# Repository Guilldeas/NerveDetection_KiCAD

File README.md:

### Content

This repo stores KiCAD files for the development of a low noise preamplifier employing the gradiometer technique. Some symbols where custom made for the schematic and were provided on the Samac_Sys folder. User must add this folder to the KiCAD library path list to correctly visualize the schematics.

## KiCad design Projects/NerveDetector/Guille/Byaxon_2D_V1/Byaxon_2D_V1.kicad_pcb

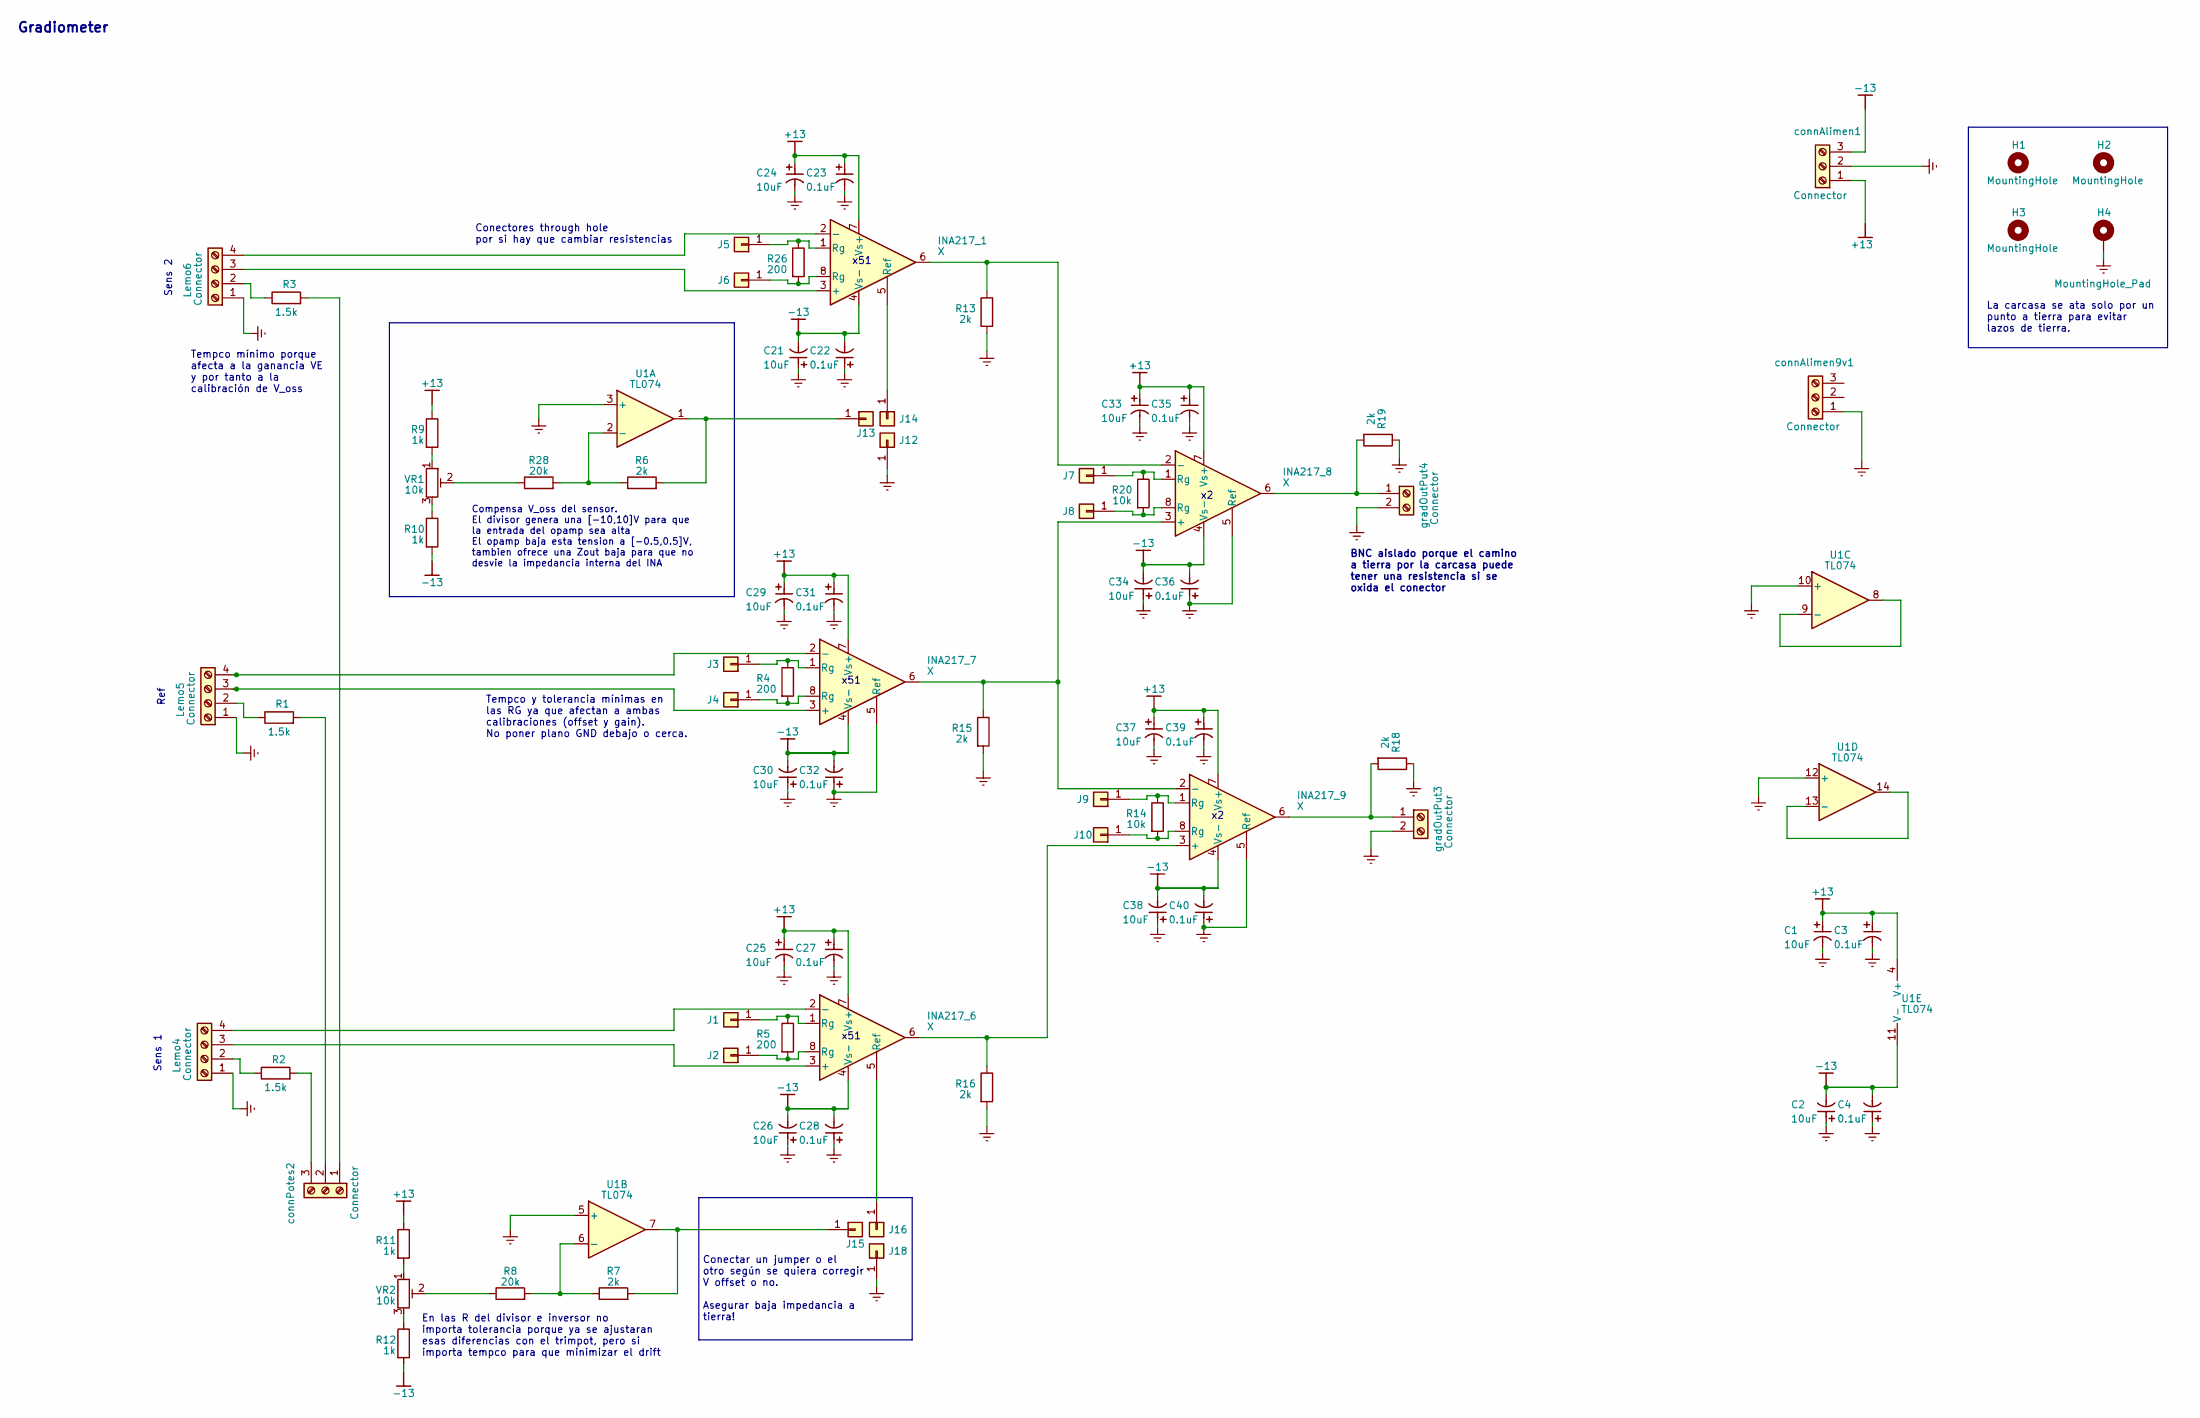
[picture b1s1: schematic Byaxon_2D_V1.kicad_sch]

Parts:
C1, C2, C21, C24, C25, C26, C29, C30, C33, C34, C37, C38: 10uF; CP_EIA-7132-20_AVX-U_Pad2.72x3.50mm_HandSolder
C3, C4, C22, C23, C27, C28, C31, C32, C35, C36, C39, C40: 0.1uF; CP_EIA-3216-10_Kemet-I_Pad1.58x1.35mm_HandSolder
H1, H2, H3: MountingHole; MountingHole_3.2mm_M3
H4: MountingHole_Pad; MountingHole_3.2mm_M3_DIN965_Pad
INA217_1, INA217_7, INA217_8, INA217_9: X; DIP-8_W7.62mm_Acid_Etch_Limitations
INA217_6: X; DIP-8_W7.62mm
J1, J2, J3, J4, J5, J6, J7, J8, J9, J10, J12, J13, J14, J15, J16, J18: Pin_D0.7mm_L6.5mm_W1.8mm_FlatFork
Lemo4, Lemo5, Lemo6: Connector; TerminalBlock_Phoenix_MPT-0,5-4-2.54_1x04_P2.54mm_Horizontal
R1, R2, R3: 1.5k; ERJ1T__2512_; Mouser Part Number 667-ERJ-1TNF1501U
R4, R5, R26: 200; RESC3016X65N; Mouser Part Number 708-RNCF1206TKY200R
R6, R7: 2k; R_0402_1005Metric_Pad0.72x0.64mm_HandSolder_Acid_Etch_Limit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; Mouser Part Number 667-ERA-2ARC202X
R8, R28: 20k; R_0402_1005Metric_Pad0.72x0.64mm_HandSolder_Acid_Etch_Limit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
R9, R10, R11, R12: 1k; RESC1608X60N; Mouser Part Number 754-RR0816P-102D
R13, R15, R16, R18, R19: 2k; RESC1005X40N_Acid_Etch_Limitations; Mouser Part Number 660-RK73H1ETTP2001F
R14, R20: 10k; RESC3016X65N; Mouser Part Number 708-RNCF1206TKY200R
U1: TL074; DIP794W53P254L1930H508Q14N_Acid_Etch_Limitations; Manufacturer_Part_Number TL074CN
VR1, VR2: 10k; 3362P_1_Acid_Etch_Limitations; Mouser Part Number 652-3362P-1-103LF
connAlimen1, connAlimen9v1: Connector; TerminalBlock_Phoenix_MPT-0,5-3-2.54_1x03_P2.54mm_Horizonta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
connPotes2: Connector; TerminalBlock_Phoenix_MPT-0,5-3-2.54_1x03_P2.54mm_Horizonta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
gradOutPut3, gradOutPut4: Connector; TerminalBlock_Phoenix_MPT-0,5-2-2.54_1x02_P2.54mm_Horizonta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

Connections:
+13: C1.2, C3.2, C23.2, C24.2, C25.2, C27.2, C29.2, C31.2, C33.2, C35.2, C37.2, C39.2, INA217_1.7 (Vs+), INA217_6.7 (Vs+), INA217_7.7 (Vs+), INA217_8.7 (Vs+), INA217_9.7 (Vs+), R9.1, R11.1, U1.4 (V+), connAlimen1.1
-13: C2.1, C4.1, C21.1, C22.1, C26.1, C28.1, C30.1, C32.1, C34.1, C36.1, C38.1, C40.1, INA217_1.4 (Vs-), INA217_6.4 (Vs-), INA217_7.4 (Vs-), INA217_8.4 (Vs-), INA217_9.4 (Vs-), R10.2, R12.2, U1.11 (V-), connAlimen1.3
Earth: C1.1, C2.2, C3.1, C4.2, C21.2, C22.2, C23.1, C24.1, C25.1, C26.2, C27.1, C28.2, C29.1, C30.2, C31.1, C32.2, C33.1, C34.2, C35.1, C36.2, C37.1, C38.2, C39.1, C40.2, H4.1, INA217_7.5 (Ref), INA217_8.5 (Ref), INA217_9.5 (Ref), J12.1, J18.1, Lemo4.1, Lemo5.1, Lemo6.1, R13.2, R15.2, R16.2, R18.1, R19.1, U1.3 (+), U1.5 (+), U1.10 (+), U1.12 (+), connAlimen1.2, connAlimen9v1.1, gradOutPut3.2, gradOutPut4.2
unnamed: INA217_1.3 (+), Lemo6.3
unnamed: INA217_1.2 (-), Lemo6.4
unnamed: INA217_1.5 (Ref), J14.1
unnamed: INA217_6.3 (+), Lemo4.3
unnamed: INA217_6.2 (-), Lemo4.4
unnamed: INA217_6.5 (Ref), J16.1
unnamed: INA217_7.3 (+), Lemo5.3
unnamed: INA217_7.2 (-), Lemo5.4
unnamed: INA217_7.6, INA217_8.3 (+), INA217_9.2 (-), R15.1
unnamed: INA217_1.6, INA217_8.2 (-), R13.1
unnamed: INA217_6.6, INA217_9.3 (+), R16.1
unnamed: INA217_6.1 (Rg), J1.1, R5.1
unnamed: INA217_6.8 (Rg), J2.1, R5.2
unnamed: INA217_7.1 (Rg), J3.1, R4.1
unnamed: INA217_7.8 (Rg), J4.1, R4.2
unnamed: INA217_1.1 (Rg), J5.1, R26.1
unnamed: INA217_1.8 (Rg), J6.1, R26.2
unnamed: INA217_8.1 (Rg), J7.1, R20.1
unnamed: INA217_8.8 (Rg), J8.1, R20.2
unnamed: INA217_9.1 (Rg), J9.1, R14.1
unnamed: INA217_9.8 (Rg), J10.1, R14.2
unnamed: J13.1, R6.2, U1.1
unnamed: J15.1, R7.2, U1.7
unnamed: Lemo4.2, R2.1
unnamed: Lemo5.2, R1.1
unnamed: Lemo6.2, R3.1
unnamed: R8.1, VR2.2
unnamed: R9.2, VR1.1
unnamed: R10.1, VR1.3
unnamed: R11.2, VR2.1
unnamed: R12.1, VR2.3
unnamed: R28.1, VR1.2
unnamed: R6.1, R28.2, U1.2 (-)
unnamed: R7.1, R8.2, U1.6 (-)
unnamed: U1.8, U1.9 (-)
unnamed: U1.13 (-), U1.14
unnamed: R3.2, connPotes2.1
unnamed: R1.2, connPotes2.2
unnamed: R2.2, connPotes2.3
unnamed: INA217_9.6, R18.2, gradOutPut3.1
unnamed: INA217_8.6, R19.2, gradOutPut4.1

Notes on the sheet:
Gradiometer
Conectar un jumper o el otro según se quiera corregir V offset o no. Asegurar baja impedancia a tierra!
Compensa V_oss del sensor. El divisor genera una [-10,10]V para que la entrada del opamp sea alta El opamp baja esta tension a [-0.5,0.5]V, tambien ofrece una Zout baja para que no desvie la impedancia interna del INA
Sens 2
La carcasa se ata solo por un punto a tierra para evitar lazos de tierra.
Conectores through hole por si hay que cambiar resistencias
x51
Sens 1
BNC aislado porque el camino a tierra por la carcasa puede tener una resistencia si se oxida el conector
Ref
Tempco mínimo porque afecta a la ganancia VE y por tanto a la calibración de V_oss
Tempco y tolerancia mínimas en las RG ya que afectan a ambas calibraciones (offset y gain). No poner plano GND debajo o cerca.
En las R del divisor e inversor no importa tolerancia porque ya se ajustaran esas diferencias con el trimpot, pero si importa tempco para que minimizar el drift

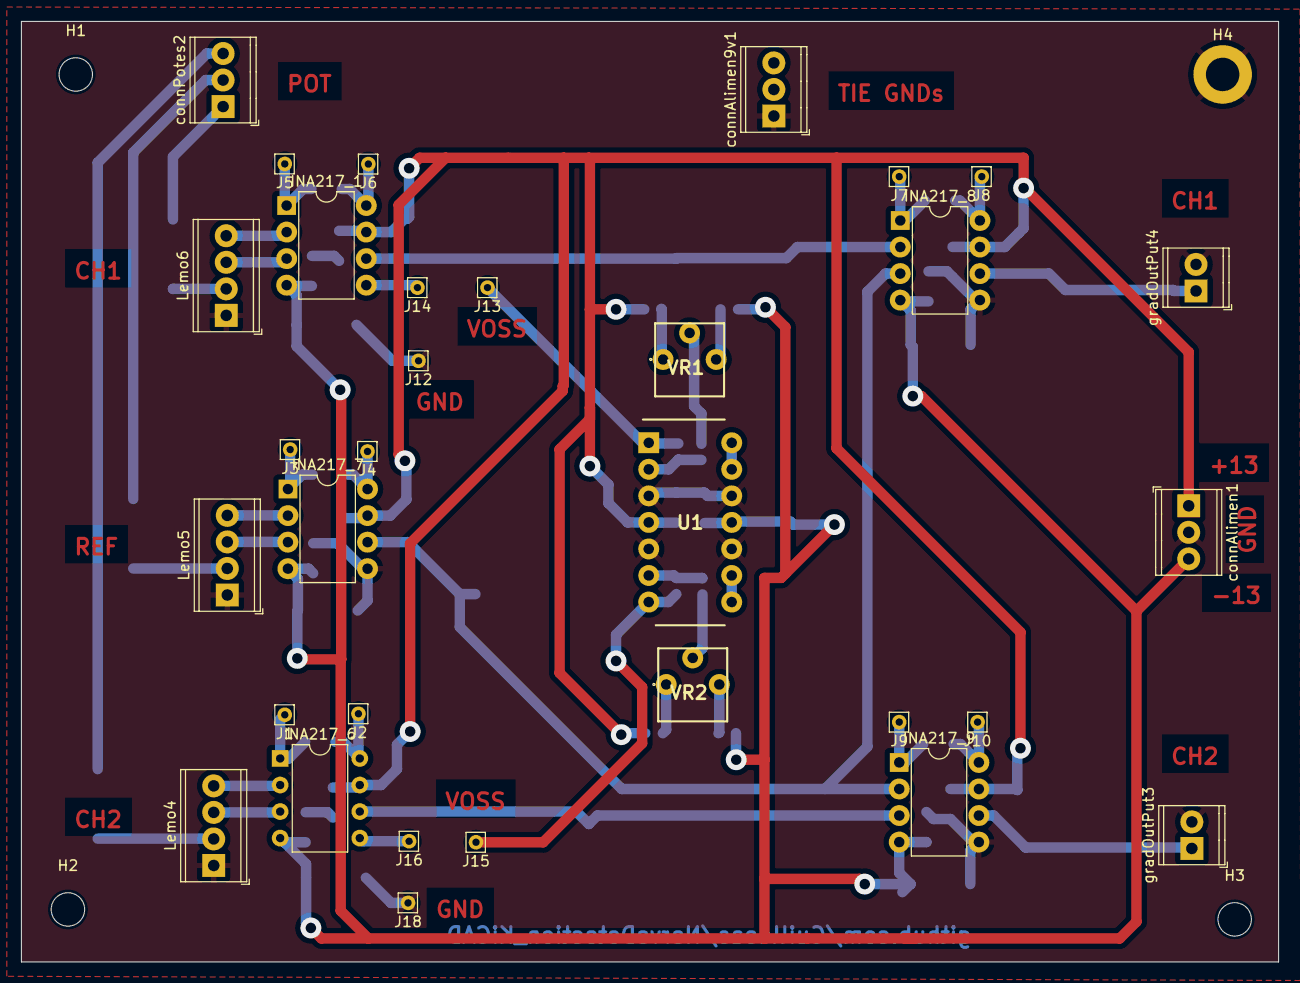
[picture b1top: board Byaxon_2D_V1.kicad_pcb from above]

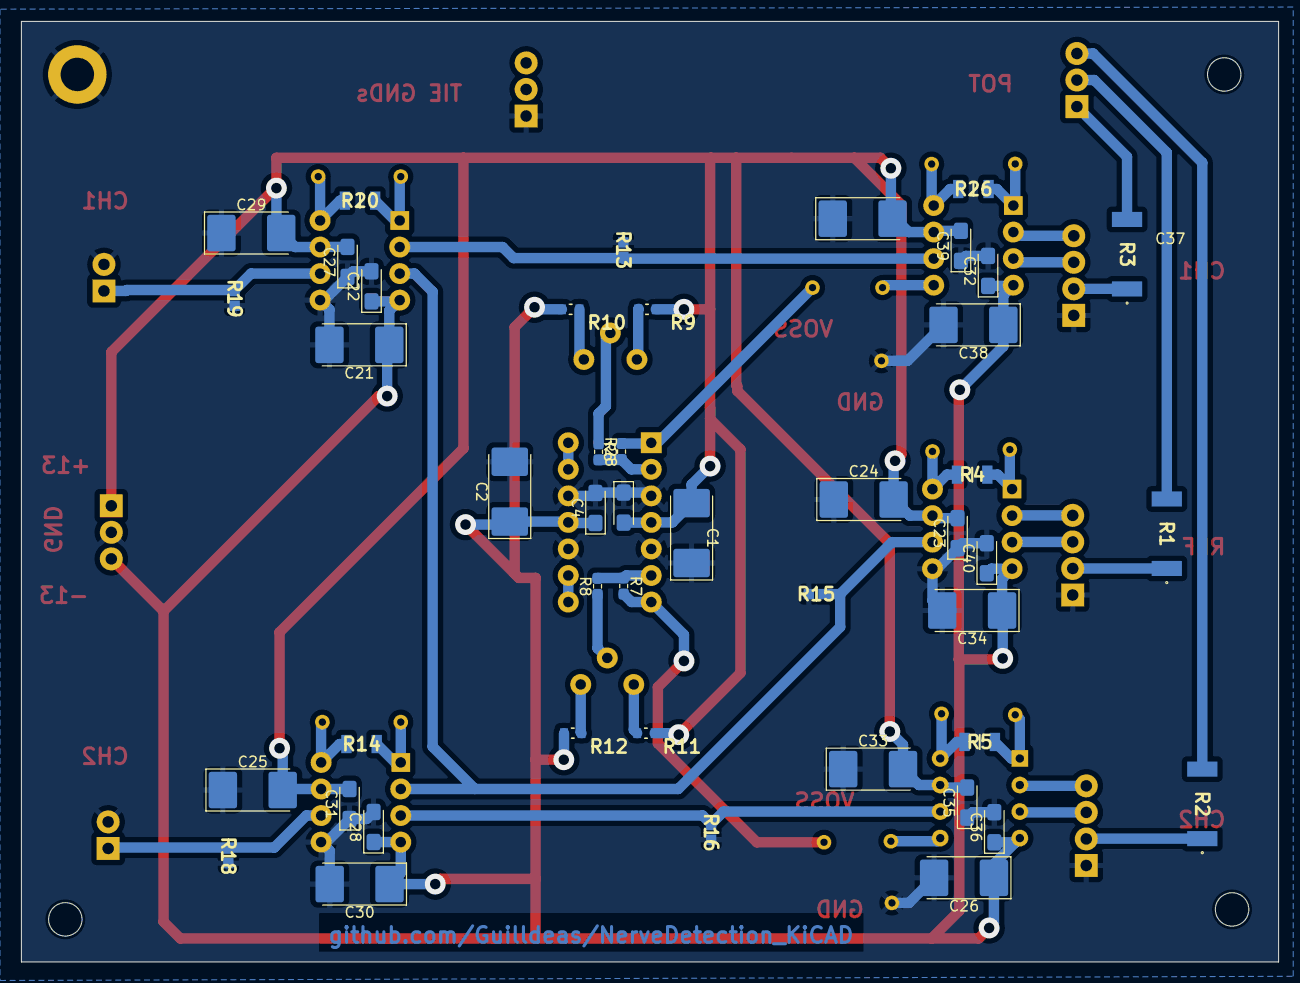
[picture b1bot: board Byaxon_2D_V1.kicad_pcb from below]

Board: 2 copper layers, 120.3 x 90.0 mm, 81 parts (45 on the bottom side), 44 nets.

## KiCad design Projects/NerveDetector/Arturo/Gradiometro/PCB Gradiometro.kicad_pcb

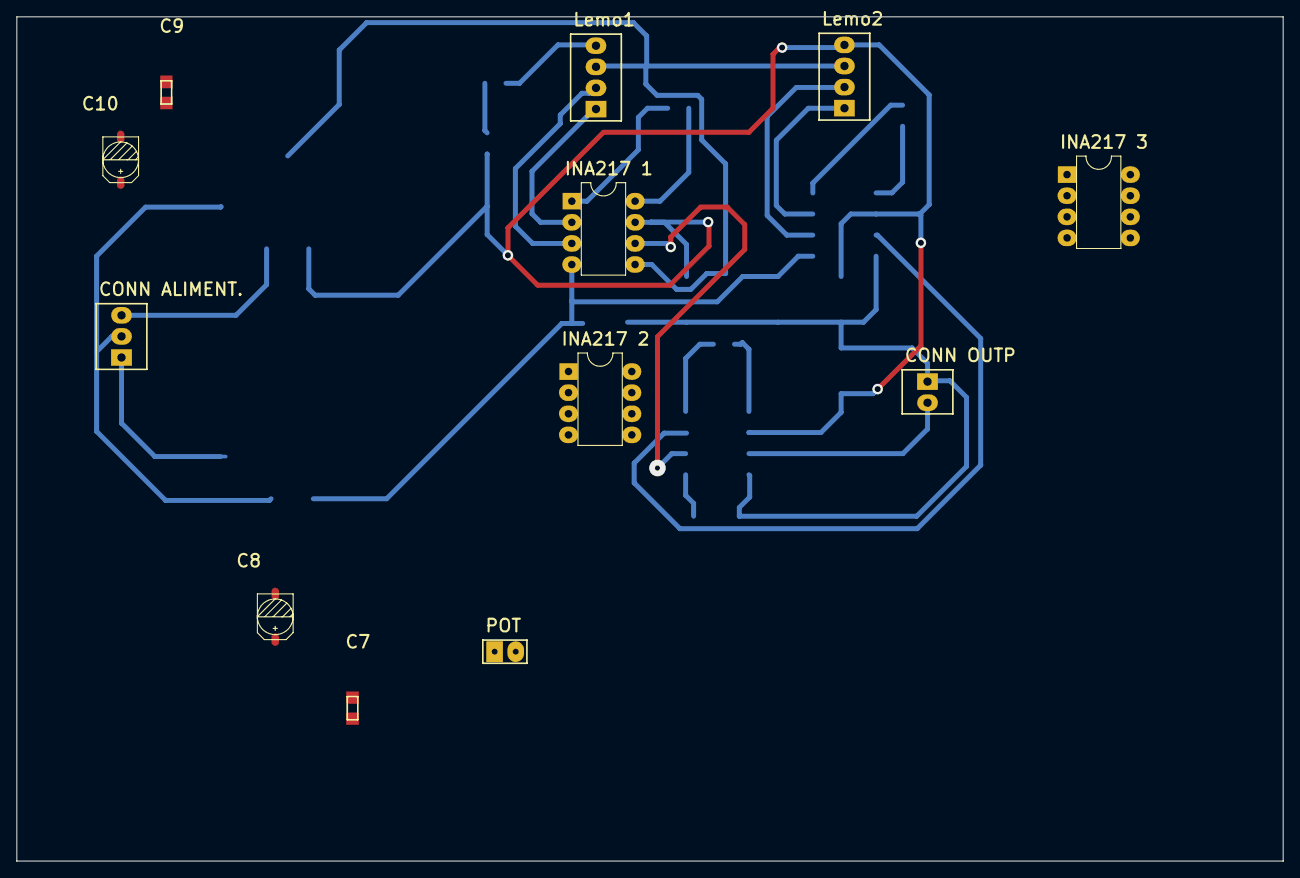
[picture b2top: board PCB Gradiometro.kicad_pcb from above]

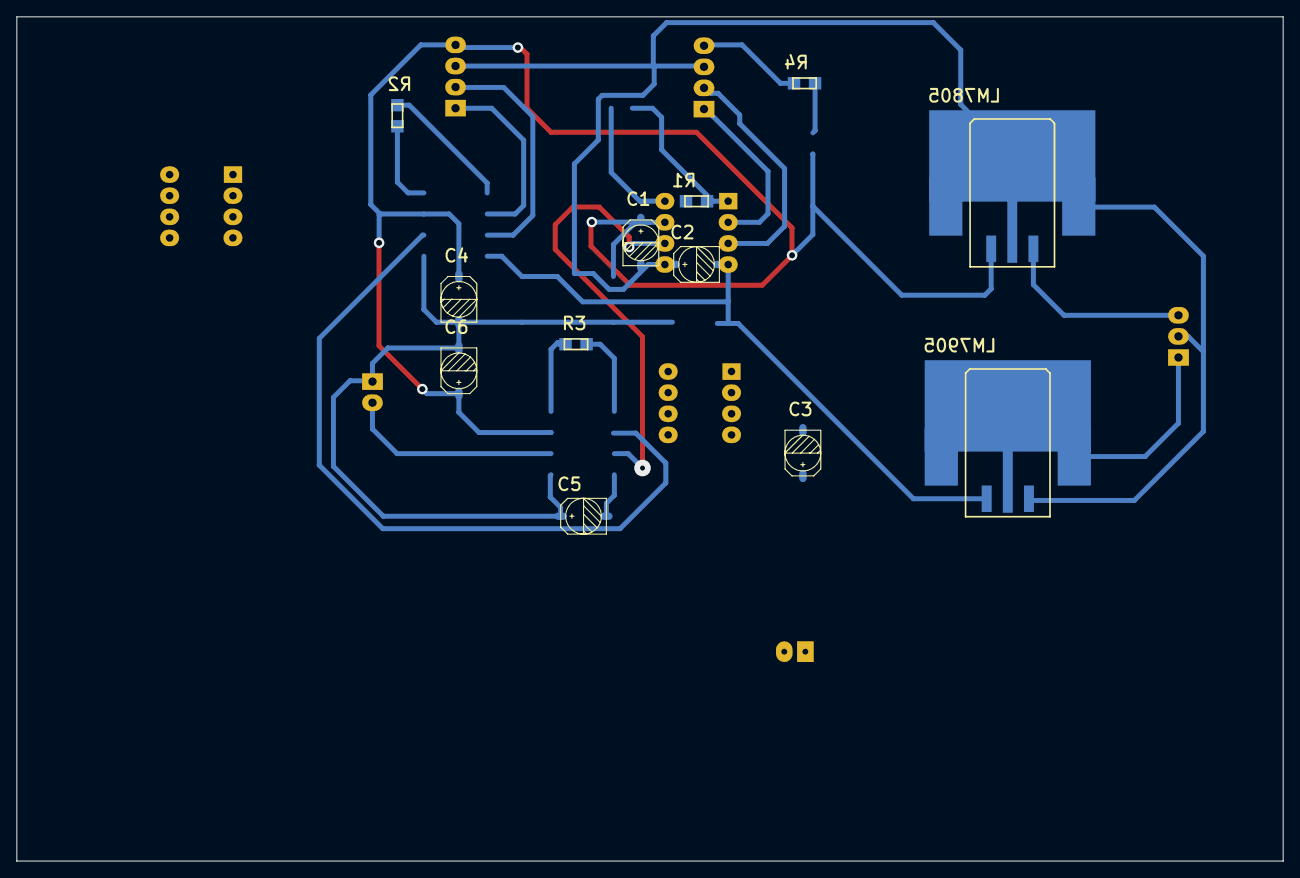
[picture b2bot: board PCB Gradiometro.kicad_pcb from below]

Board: 2 copper layers, 152.4 x 101.6 mm, 24 parts (12 on the bottom side), 20 nets.

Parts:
C1, C4, C6: 10 uF; C SMD Electrolytic
C2, C3, C5: 10uF; C SMD Electrolytic
C7: 2.2uF; SMD0805
C8: 1uF; C SMD Electrolytic
C9: 0.33uF; SMD0805
C10: 0.1uF; C SMD Electrolytic
CONN ALIMENT.: Connector; Bloque.Ter. 3
CONN OUTP: Connector; Bloque.Ter. 2
INA217 1, INA217 2, INA217 3: X; DIP 8
LM7805: LM78XX; 7805 Smd
LM7905: LM78XX; 7905 SMD
Lemo1, Lemo2: Connector; Bloque.Ter. 4
POT: Connector; Tira 2 Pines
R1, R2: 204 Ohm; SMD0805
R3: 111 Ohm; SMD0805
R4: Value; SMD0805

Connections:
+5: C1.2, C4.2, C6.2, C10.2, INA217 1.7, INA217 2.7, INA217 3.7, LM7805.Vout, Lemo2.4, POT.2
-5: C2.1, C3.1, C5.1, C8.1, INA217 1.4, INA217 2.4, INA217 3.4, LM7905.Vout
GND: C1.1, C2.2, C3.2, C4.1, C5.2, C6.1, C7.1, C8.2, C9.1, C10.1, CONN ALIMENT..2, CONN OUTP.1, INA217 1.5, INA217 2.5, INA217 3.5, LM7805.GND, LM7905.GND, Lemo1.3, Lemo2.3
NetC7_2: C7.2, CONN ALIMENT..1, LM7905.Vin
NetC9_2: C9.2, CONN ALIMENT..3, LM7805.Vin
NetCONN OUTP_2: CONN OUTP.2, INA217 3.6
NetINA217 1_1: INA217 1.1, R1.1
NetINA217 1_2: INA217 1.2, Lemo1.1
NetINA217 1_3: INA217 1.3, Lemo1.2
NetINA217 1_6: INA217 1.6, INA217 3.3
NetINA217 1_8: INA217 1.8, R1.2
NetINA217 2_1: INA217 2.1, R2.1
NetINA217 2_2: INA217 2.2, Lemo2.1
NetINA217 2_3: INA217 2.3, Lemo2.2
NetINA217 2_6: INA217 2.6, INA217 3.2
NetINA217 2_8: INA217 2.8, R2.2
NetINA217 3_1: INA217 3.1, R3.1
NetINA217 3_8: INA217 3.8, R3.2
NetLemo1_4: Lemo1.4, R4.2
NetPOT_1: POT.1, R4.1

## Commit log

2023-07-27 Got files properly sorted into folders
2023-07-27 Solved problem with footprint libraries missing
2023-07-27 Layed out bigger edge cut, added jumper to Voss
2023-07-28 Changed jumpers + some layout
2023-07-28 Final commit of the day - Some layout
2023-07-31 Finished layout
2023-07-31 Added link to projects github on the PCB
2023-08-01 Added mounting holes
